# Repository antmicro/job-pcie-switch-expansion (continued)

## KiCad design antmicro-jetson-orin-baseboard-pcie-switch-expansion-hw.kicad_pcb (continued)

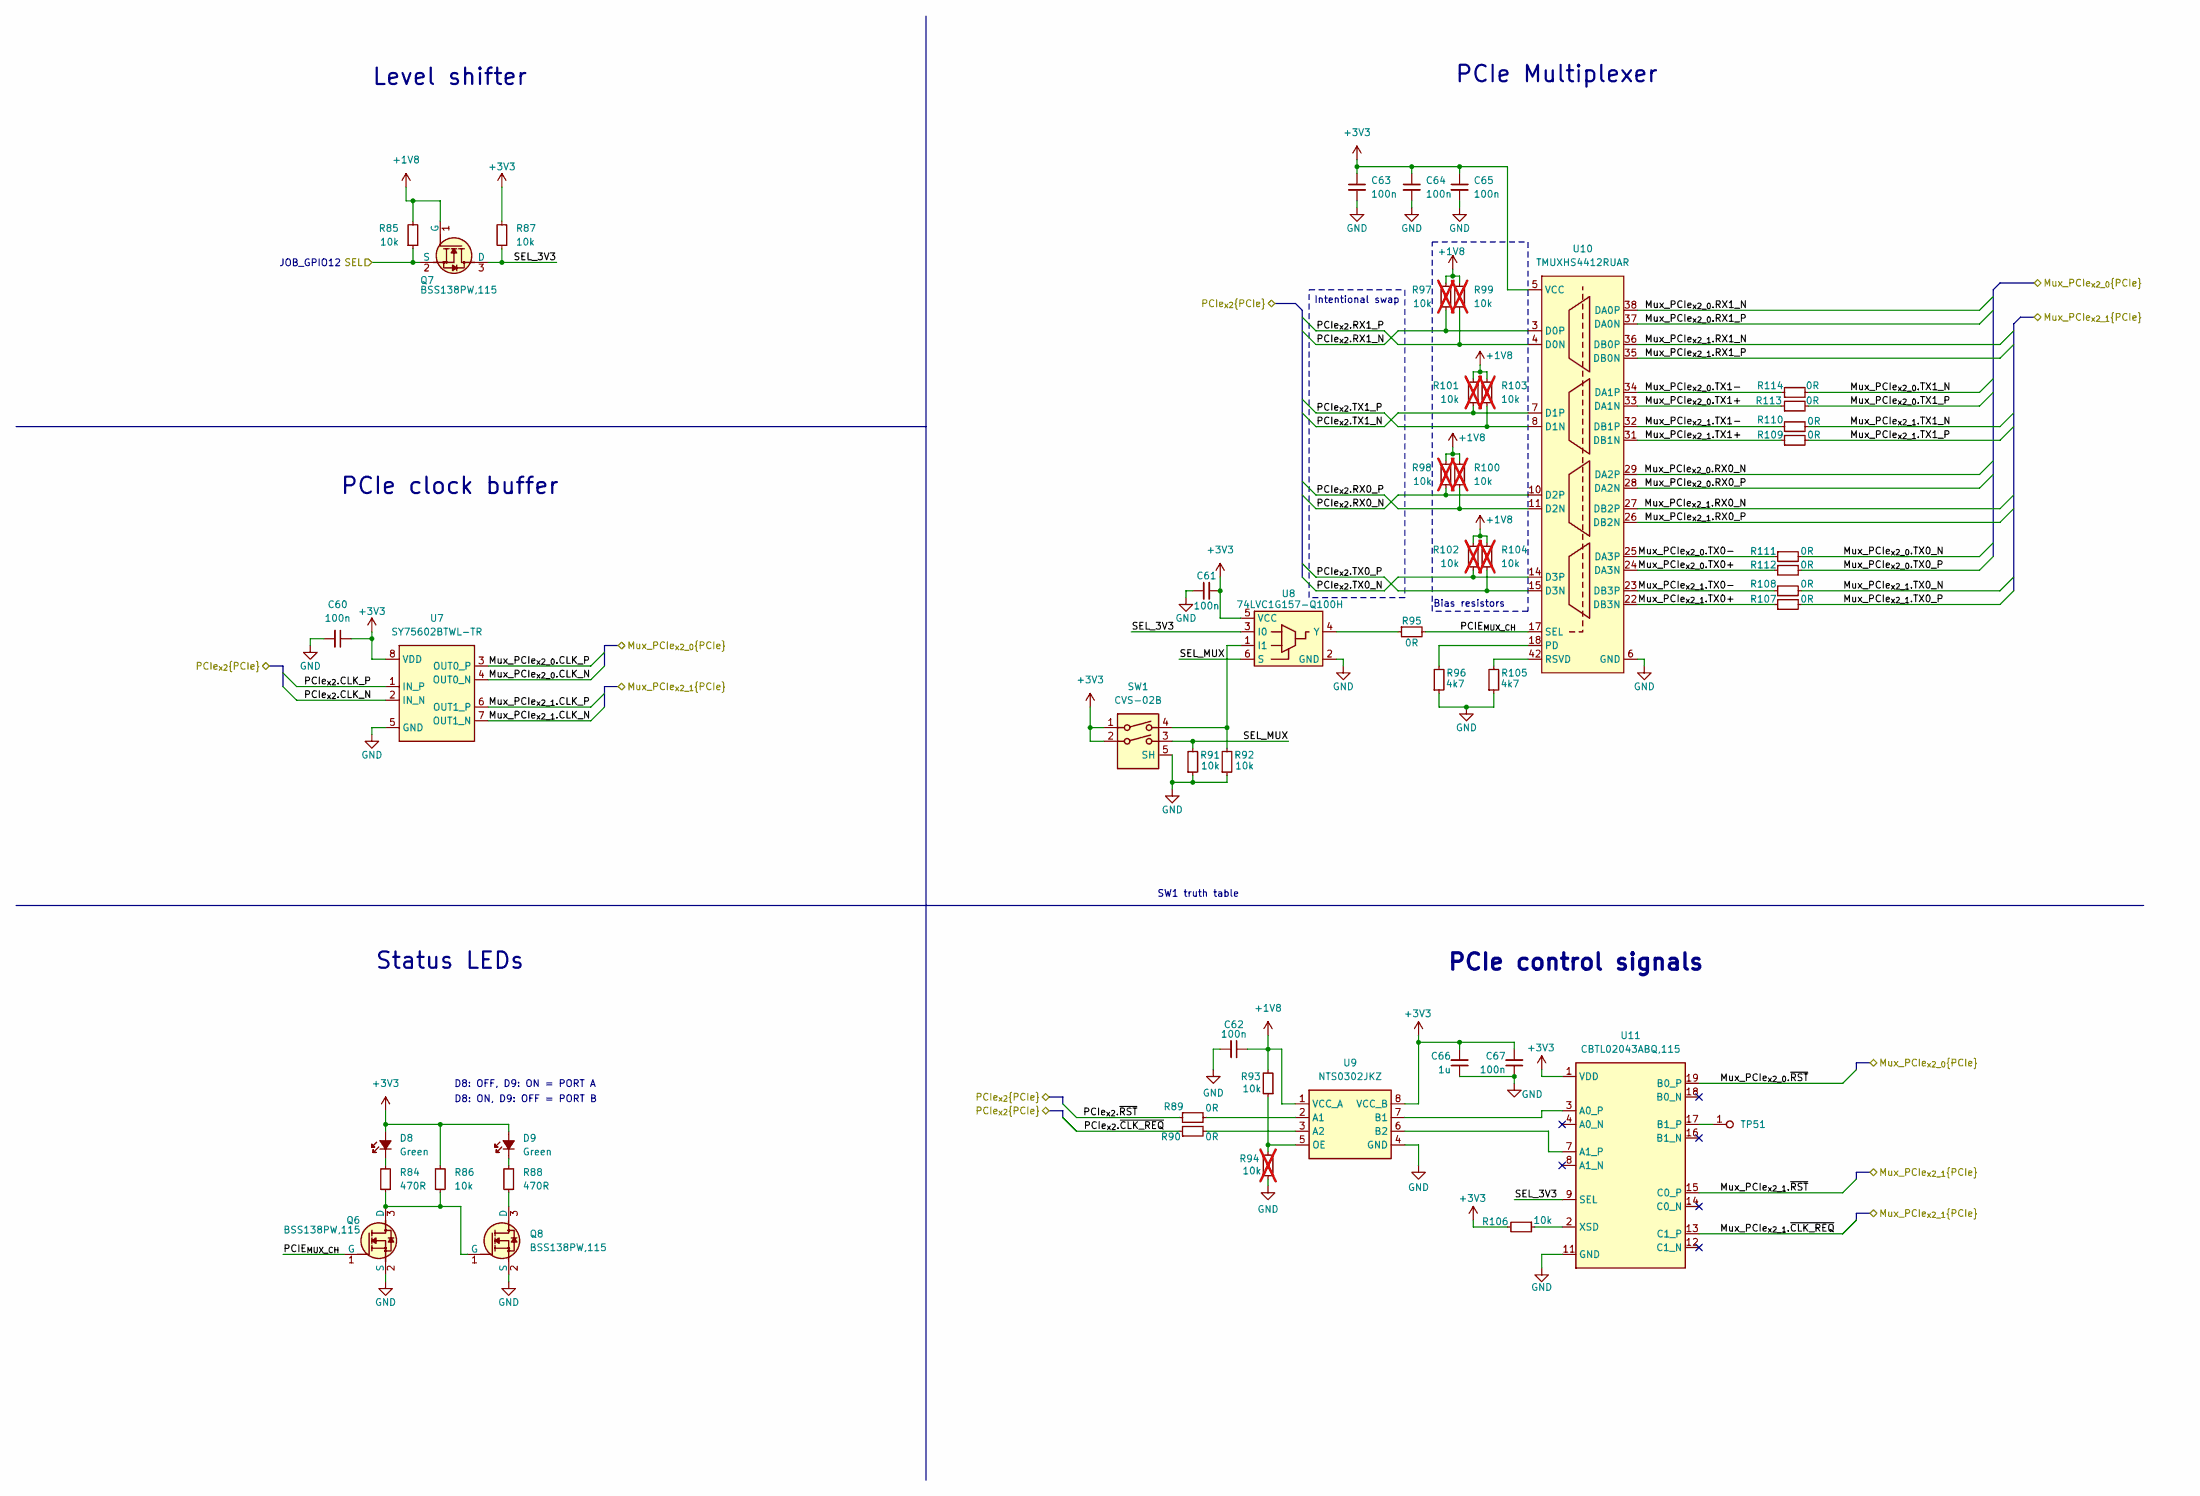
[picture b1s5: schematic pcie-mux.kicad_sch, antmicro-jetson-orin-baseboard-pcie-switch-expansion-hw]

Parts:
C60, C61, C62, C63, C64, C65, C67: C_100n_0402; C_0402_1005Metric; Voltage 50V; MPN GRM155R61H104KE14D
C66: C_1u_0402; C_0402_1005Metric; MPN C1005X6S1A105K050BC
D8, D9: LED_G_0603_LG_L29K-G2J1-24-Z; LED_0603_1608Metric_G; MPN LG L29K-G2J1-24-Z
Q6, Q7, Q8: BSS138PW,115; SC70-3; MPN BSS138PW,115
R84, R88: R_470R_0402; R_0402_1005Metric; Tolerance 1%; MPN CR0402-FX-4700GLF
R85, R86, R87, R91, R92, R93, R106: R_10k_0402; R_0402_1005Metric; Tolerance 1%; MPN CR0402-FX-1002GLF
R89, R90, R95, R107, R108, R109, R110, R111, R112, R113, R114: R_0R_0402; R_0402_1005Metric; MPN ERJ2GE0R00X
R94, R97, R98, R99, R100, R101, R102, R103, R104: R_10k_0402; R_0402_1005Metric; Tolerance 1%; MPN CR0402-FX-1002GLF; not fitted
R96, R105: R_4k7_0402; R_0402_1005Metric; Tolerance 1%; MPN CR0402-FX-4701GLF
SW1: SW_CVS-02B; SW_DIP_SPSTx02_Slide_Copal_CVS-02xB_W5.9mm_P1mm; MPN CVS-02B
TP51: TP_1mm_SMD; TP_SMD_1mm
U7: SY75602BTWL-TR; VDFN-8_1.6x1.4mm_P0.4mm; MPN SY75602BTWL-TR
U8: 74LVC1G157-Q100H_SOT457; SC-74-6_1.5x2.9mm_P0.95mm; MPN 74LVC1G157-Q100H
U9: NTS0302JKZ; X2SON8_1.4x1x0.32mm_P0.35mm; MPN NTS0302JKZ
U10: TMUXHS4412RUAR; WQFN-42-1EP_3.5x9mm_P0.5mm; MPN TMUXHS4412RUAR
U11: CBTL02043ABQ; DHVQFN-20-1EP_2.5x4.5_P0.5mm; MPN CBTL02043ABQ,115

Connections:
+1V8: C62.1, Q7.1 (G), R85.2, R93.2, R97.2, R98.2, R99.2, R100.2, R101.2, R102.2, R103.2, R104.2, U9.1 (VCC_A); also elsewhere on the board
+3V3: C60.1, C61.2, C63.1, C64.1, C65.1, C66.2, C67.2, D8.2 (A), D9.2 (A), R86.2, R87.2, R106.2, SW1.1, SW1.2, U7.8 (VDD), U8.5 (VCC), U9.8 (VCC_B), U10.5 (VCC), U10.13 (VCC), U11.1 (VDD), U11.6 (VDD), U11.10 (VDD); also elsewhere on the board
/Expansion Connector/SEL: Q7.2 (S), R85.1; also elsewhere on the board
/M.2 port B/PCIe_{x2}.CLK_N: U7.7 (OUT1_N); also elsewhere on the board
/M.2 port B/PCIe_{x2}.CLK_P: U7.6 (OUT1_P); also elsewhere on the board
/M.2 port B/PCIe_{x2}.RX0_N: U10.27 (DB2P); also elsewhere on the board
/M.2 port B/PCIe_{x2}.RX0_P: U10.26 (DB2N); also elsewhere on the board
/M.2 port B/PCIe_{x2}.RX1_N: U10.36 (DB0P); also elsewhere on the board
/M.2 port B/PCIe_{x2}.RX1_P: U10.35 (DB0N); also elsewhere on the board
/M.2 port B/PCIe_{x2}.TX0_N: R108.2; also elsewhere on the board
/M.2 port B/PCIe_{x2}.TX0_P: R107.2; also elsewhere on the board
/M.2 port B/PCIe_{x2}.TX1_N: R110.2; also elsewhere on the board
/M.2 port B/PCIe_{x2}.TX1_P: R109.2; also elsewhere on the board
/M.2 port B/PCIe_{x2}.~CLK_REQ: U11.13 (C1_P); also elsewhere on the board
/M.2 port B/PCIe_{x2}.~RST: U11.15 (C0_P); also elsewhere on the board
/OCuLink/PCIe_{x2}.CLK_N: U7.4 (OUT0_N); also elsewhere on the board
/OCuLink/PCIe_{x2}.CLK_P: U7.3 (OUT0_P); also elsewhere on the board
/OCuLink/PCIe_{x2}.RX0_N: U10.29 (DA2P); also elsewhere on the board
/OCuLink/PCIe_{x2}.RX0_P: U10.28 (DA2N); also elsewhere on the board
/OCuLink/PCIe_{x2}.RX1_N: U10.38 (DA0P); also elsewhere on the board
/OCuLink/PCIe_{x2}.RX1_P: U10.37 (DA0N); also elsewhere on the board
/OCuLink/PCIe_{x2}.TX0_N: R111.2; also elsewhere on the board
/OCuLink/PCIe_{x2}.TX0_P: R112.2; also elsewhere on the board
/OCuLink/PCIe_{x2}.TX1_N: R114.2; also elsewhere on the board
/OCuLink/PCIe_{x2}.TX1_P: R113.2; also elsewhere on the board
/OCuLink/PCIe_{x2}.~RST: U11.19 (B0_P); also elsewhere on the board
/PCIe Mux/Mux_PCIe_{x2_0}.TX0+: R112.1, U10.24 (DA3N)
/PCIe Mux/Mux_PCIe_{x2_0}.TX0-: R111.1, U10.25 (DA3P)
/PCIe Mux/Mux_PCIe_{x2_0}.TX1+: R113.1, U10.33 (DA1N)
/PCIe Mux/Mux_PCIe_{x2_0}.TX1-: R114.1, U10.34 (DA1P)
/PCIe Mux/Mux_PCIe_{x2_1}.TX0+: R107.1, U10.22 (DB3N)
/PCIe Mux/Mux_PCIe_{x2_1}.TX0-: R108.1, U10.23 (DB3P)
/PCIe Mux/Mux_PCIe_{x2_1}.TX1+: R109.1, U10.31 (DB1N)
/PCIe Mux/Mux_PCIe_{x2_1}.TX1-: R110.1, U10.32 (DB1P)
/PCIe Mux/PCIE_{MUX_CH}: Q6.1 (G), R95.2, U10.17 (SEL)
/PCIe Mux/PCIe_{x2}.CLK_N: U7.2 (IN_N); also elsewhere on the board
/PCIe Mux/PCIe_{x2}.CLK_P: U7.1 (IN_P); also elsewhere on the board
/PCIe Mux/PCIe_{x2}.RX0_N: R98.1, U10.10 (D2P); also elsewhere on the board
/PCIe Mux/PCIe_{x2}.RX0_P: R100.1, U10.11 (D2N); also elsewhere on the board
/PCIe Mux/PCIe_{x2}.RX1_N: R97.1, U10.3 (D0P); also elsewhere on the board
/PCIe Mux/PCIe_{x2}.RX1_P: R99.1, U10.4 (D0N); also elsewhere on the board
/PCIe Mux/PCIe_{x2}.TX0_N: R102.1, U10.14 (D3P); also elsewhere on the board
/PCIe Mux/PCIe_{x2}.TX0_P: R104.1, U10.15 (D3N); also elsewhere on the board
/PCIe Mux/PCIe_{x2}.TX1_N: R101.1, U10.7 (D1P); also elsewhere on the board
/PCIe Mux/PCIe_{x2}.TX1_P: R103.1, U10.8 (D1N); also elsewhere on the board
/PCIe Mux/PCIe_{x2}.~CLK_REQ: R90.1; also elsewhere on the board
/PCIe Mux/PCIe_{x2}.~RST: R89.1; also elsewhere on the board
/PCIe Mux/SEL_3V3: Q7.3 (D), R87.1, U8.3 (I0), U11.9 (SEL)
/PCIe Mux/SEL_MUX: R91.2, SW1.3, U8.6 (S)
GND: C60.2, C61.1, C62.2, C63.2, C64.2, C65.2, C66.1, C67.1, Q6.2 (S), Q8.2 (S), R91.1, R92.1, R94.1, R96.1, R105.1, SW1.5 (SH_5), U7.5 (GND), U8.2 (GND), U9.4 (GND), U10.6 (GND), U10.9 (GND), U10.16 (GND), U10.21 (GND), U10.30 (GND), U10.39 (GND), U10.43 (GND), U11.5 (GND), U11.11 (GND), U11.20 (GND), U11.21 (GND); also elsewhere on the board
unnamed: D8.1 (C), R84.2
unnamed: D9.1 (C), R88.2
unnamed: Q6.3 (D), Q8.1 (G), R84.1, R86.1
unnamed: Q8.3 (D), R88.1
unnamed: R92.2, SW1.4, U8.1 (I1)
unnamed: R95.1, U8.4 (Y)
unnamed: R89.2, U9.2 (A1)
unnamed: R90.2, U9.3 (A2)
unnamed: R93.1, R94.2, U9.5 (OE)
unnamed: R96.2, U10.18 (PD)
unnamed: R105.2, U10.42 (RSVD)
unnamed: U9.7 (B1), U11.3 (A0_P)
unnamed: U9.6 (B2), U11.7 (A1_P)
unnamed: TP51.1 (1_1), U11.17 (B1_P)
unnamed: R106.1, U11.2 (XSD)

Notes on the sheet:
JOB_GPIO12
Level shifter
PCIe clock buffer
SW1 truth table
PCIe Multiplexer
Bias resistors
Intentional swap
D8: OFF, D9: ON = PORT A
Status LEDs
D8: ON, D9: OFF = PORT B
PCIe control signals

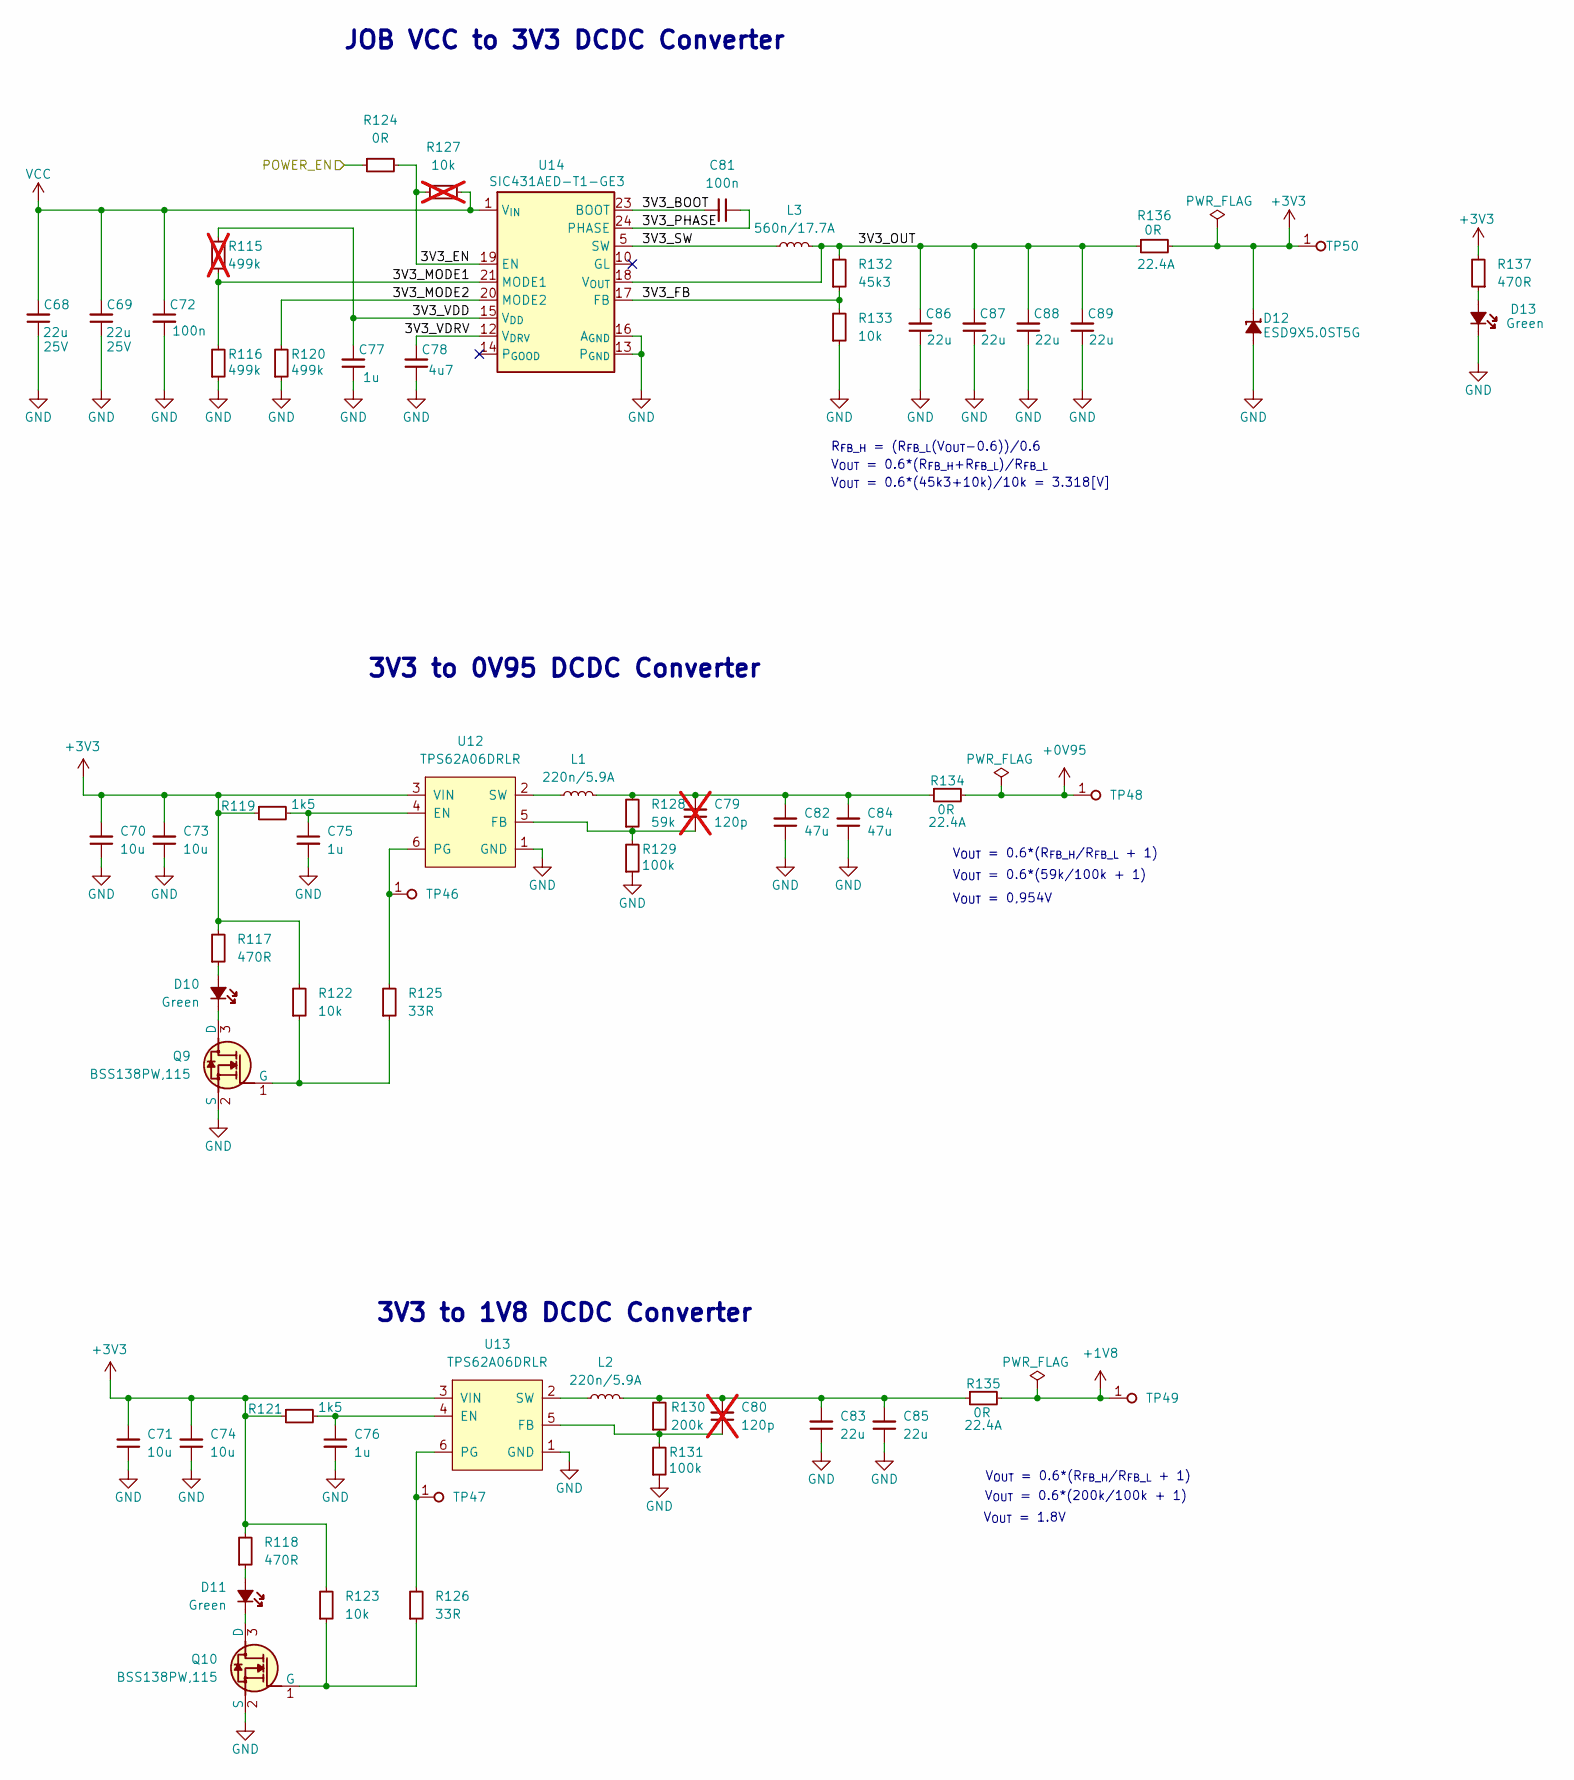
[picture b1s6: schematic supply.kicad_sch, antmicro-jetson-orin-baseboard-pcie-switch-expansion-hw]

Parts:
C68, C69: C_22u_25V_0805; C_0805_2012Metric; Voltage 25V; MPN CL21A226MAYNNNE
C70, C71, C73, C74: C_10u_0402; C_0402_1005Metric; MPN CC0402MRX5R5BB106
C72, C81: C_100n_0402; C_0402_1005Metric; Voltage 50V; MPN GRM155R61H104KE14D
C75, C76, C77: C_1u_0402; C_0402_1005Metric; MPN C1005X6S1A105K050BC
C78: C_4u7_25V_0402; C_0402_1005Metric; Voltage 25V; MPN GRM155C61E475ME15J
C79, C80: C_120p_100V_0402; C_0402_1005Metric; Voltage 100V; MPN C0402C121J5GACTU; not fitted
C82, C84: C_47u_0603; C_0603_1608Metric; MPN GRM188R60J476ME15D
C83, C85: C_22u_0603; C_0603_1608Metric; MPN GRM188R60J226MEA0D
C86, C87, C88, C89: C_22u_16V_0603; C_0603_1608Metric_EIA; Voltage 16V; MPN CL10A226MO7JZNC
D10, D11: LED_G_0603_LG_L29K-G2J1-24-Z; LED_0603_1608Metric_G; MPN LG L29K-G2J1-24-Z
D12: ESD9X5.0ST5G; SOD-923; MPN ESD9X5.0ST5G
D13: LED_G_0603_KP-1608CGCK; LED_0603_1608Metric_G; MPN KP-1608CGCK
L1, L2: L_220n_5.9A_1008; L_1008_2520Metric; MPN SRP2510TMA-R22M
L3: L_560n_17.7A_Bourns-SRP5030CA; L_Bourns-SRP5030CA; MPN SRP5030CA-R56M
Q9, Q10: BSS138PW,115; SC70-3; MPN BSS138PW,115
R115: R_499k_0402; R_0402_1005Metric; Tolerance 1%; MPN CR0402-FX-4993GLF; not fitted
R116, R120: R_499k_0402; R_0402_1005Metric; Tolerance 1%; MPN CR0402-FX-4993GLF
R117, R118, R137: R_470R_0402; R_0402_1005Metric; Tolerance 1%; MPN CR0402-FX-4700GLF
R119, R121: R_1k5_0402; R_0402_1005Metric; Tolerance 1%; MPN CR0402-FX-1501GLF
R122, R123, R133: R_10k_0402; R_0402_1005Metric; Tolerance 1%; MPN CR0402-FX-1002GLF
R124: R_0R_0402; R_0402_1005Metric; MPN ERJ2GE0R00X
R125, R126: R_33R_0402; R_0402_1005Metric; Tolerance 1%; MPN CR0402-FX-33R0GLF
R127: R_10k_0402; R_0402_1005Metric; Tolerance 1%; MPN CR0402-FX-1002GLF; not fitted
R128: R_59k_0402; R_0402_1005Metric; Tolerance 1%; MPN CR0402-FX-5902GLF
R129, R131: R_100k_0.1%_0402; R_0402_1005Metric; Tolerance 1%; MPN CR0402-FX-1003GLF
R130: R_200k_0402; R_0402_1005Metric; Tolerance 1%; MPN CR0402-FX-2003GLF
R132: R_45k3_0402; R_0402_1005Metric; Tolerance 1%; MPN CR0402-FX-4532GLF
R134, R135, R136: R_0R_22.4A_0603; R_0603_1608Metric; Tolerance template_tolerance; MPN PMR03EZPJ000
TP46, TP47, TP48, TP49, TP50: TP_0.75mm_SMD; TP_SMD_0.75mm
U12, U13: TPS62A06DRLR; SOT-563; MPN TPS62A06DRLR
U14: SIC431AED-T1-GE3; MLP44-24L_4x4x0.75mm; MPN SIC431AED-T1-GE3

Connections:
+0V95: R134.2, TP48.1 (1_1); also elsewhere on the board
+1V8: R135.2, TP49.1 (1_1); also elsewhere on the board
+3V3: C70.2, C71.2, C73.2, C74.2, D12.1 (C), R117.2, R118.2, R119.1, R121.1, R122.2, R123.2, R136.2, R137.2, TP50.1 (1_1), U12.3 (VIN), U13.3 (VIN); also elsewhere on the board
/Expansion Connector/POWER_EN: R124.1; also elsewhere on the board
/Supply/3V3_BOOT: C81.2, U14.23 (BOOT)
/Supply/3V3_EN: R124.2, R127.2, U14.19 (EN)
/Supply/3V3_FB: R132.1, R133.2, U14.17 (FB)
/Supply/3V3_MODE1: R115.1, R116.2, U14.21 (MODE1)
/Supply/3V3_MODE2: R120.2, U14.20 (MODE2)
/Supply/3V3_OUT: C86.2, C87.2, C88.2, C89.2, L3.2, R132.2, R136.1, U14.18 (V_{OUT})
/Supply/3V3_PHASE: C81.1, U14.24 (PHASE)
/Supply/3V3_SW: L3.1, U14.5 (SW), U14.6 (SW), U14.7 (SW), U14.8 (SW), U14.9 (SW)
/Supply/3V3_VDD: C77.2, R115.2, U14.15 (V_{DD})
/Supply/3V3_VDRV: C78.2, U14.12 (V_{DRV})
GND: C68.1, C69.1, C70.1, C71.1, C72.2, C73.1, C74.1, C75.2, C76.2, C77.1, C78.1, C82.1, C83.1, C84.1, C85.1, C86.1, C87.1, C88.1, C89.1, D12.2 (A), D13.1 (C), Q9.2 (S), Q10.2 (S), R116.1, R120.1, R129.1, R131.1, R133.1, U12.1 (GND), U13.1 (GND), U14.3 (P_{GND}), U14.4 (P_{GND}), U14.13 (P_{GND}), U14.16 (A_{GND}), U14.25 (A_{GND}), U14.27 (P_{GND}); also elsewhere on the board
unnamed: C79.2, C82.2, C84.2, L1.2, R128.2, R134.1
unnamed: C80.2, C83.2, C85.2, L2.2, R130.2, R135.1
unnamed: D10.2 (A), R117.1
unnamed: D10.1 (C), Q9.3 (D)
unnamed: D11.2 (A), R118.1
unnamed: D11.1 (C), Q10.3 (D)
unnamed: D13.2 (A), R137.1
unnamed: Q9.1 (G), R122.1, R125.1
unnamed: Q10.1 (G), R123.1, R126.1
unnamed: C75.1, R119.2, U12.4 (EN)
unnamed: C79.1, R128.1, R129.2, U12.5 (FB)
unnamed: R125.2, TP46.1 (1_1), U12.6 (PG)
unnamed: L1.1, U12.2 (SW)
unnamed: C76.1, R121.2, U13.4 (EN)
unnamed: C80.1, R130.1, R131.2, U13.5 (FB)
unnamed: R126.2, TP47.1 (1_1), U13.6 (PG)
unnamed: L2.1, U13.2 (SW)
VCC: C68.2, C69.2, C72.1, R127.1, U14.1 (V_{IN}), U14.2 (V_{IN}), U14.22 (V_{IN}), U14.26 (V_{IN}); also elsewhere on the board

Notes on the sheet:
3V3 to 1V8 DCDC Converter
V_{OUT} = 0.6*(R_{FB_H}+R_{FB_L})/R_{FB_L}
R_{FB_H} = (R_{FB_L}(V_{OUT}-0.6))/0.6
V_{OUT} = 0.6*(45k3+10k)/10k = 3.318[V]
V_{OUT} = 0.6*(R_{FB_H}/R_{FB_L} + 1)
V_{OUT} = 0.6*(59k/100k + 1)
3V3 to 0V95 DCDC Converter
JOB VCC to 3V3 DCDC Converter
V_{OUT} = 0,954V
V_{OUT} = 1.8V
V_{OUT} = 0.6*(200k/100k + 1)

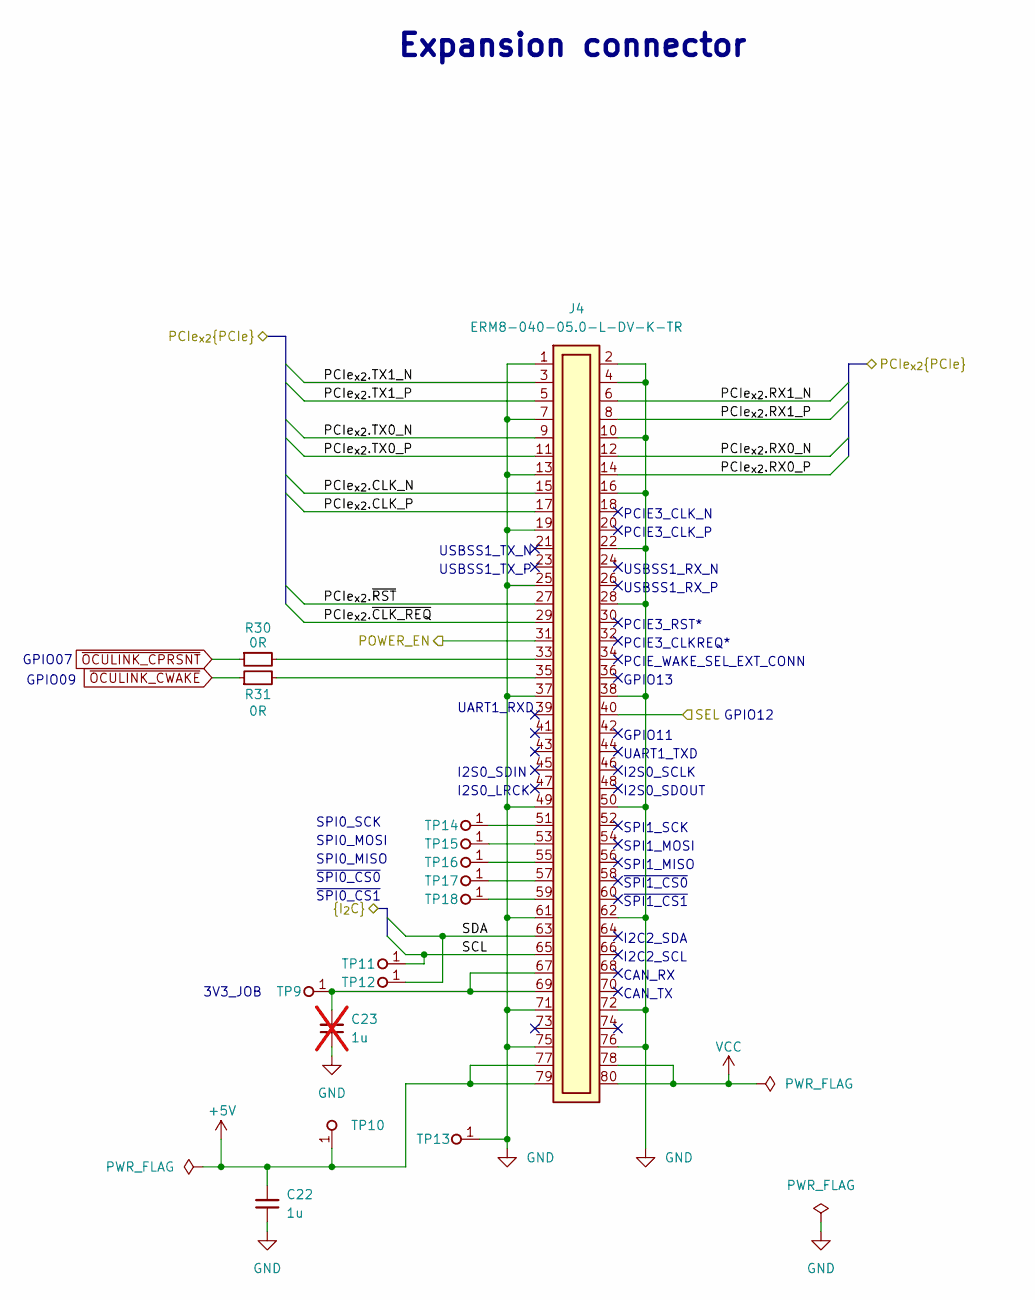
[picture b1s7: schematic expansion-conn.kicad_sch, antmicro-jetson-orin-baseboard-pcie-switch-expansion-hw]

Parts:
C22: C_1u_0402; C_0402_1005Metric; MPN C1005X6S1A105K050BC
C23: C_1u_0402; C_0402_1005Metric; MPN C1005X6S1A105K050BC; not fitted
J4: Plug_Samtec_ERM8_2x40_ERM8-040-05.0-L-DV-K-TR; Conn_Plug_Samtec_ERM8_2x40_ERM8-040-05.0-L-DV-K-TR; MPN ERM8-040-05.0-L-DV-K-TR
R30, R31: R_0R_0402; R_0402_1005Metric; MPN ERJ2GE0R00X
TP9, TP10, TP11, TP12, TP13, TP14, TP15, TP16, TP17, TP18: TP_0.75mm_SMD; TP_SMD_0.75mm

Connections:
+5V: C22.2, J4.77, J4.79, TP10.1 (1_1); also elsewhere on the board
/Expansion Connector/PCIe_{x2}.CLK_N: J4.15; also elsewhere on the board
/Expansion Connector/PCIe_{x2}.CLK_P: J4.17; also elsewhere on the board
/Expansion Connector/PCIe_{x2}.RX0_N: J4.12; also elsewhere on the board
/Expansion Connector/PCIe_{x2}.RX0_P: J4.14; also elsewhere on the board
/Expansion Connector/PCIe_{x2}.RX1_N: J4.6; also elsewhere on the board
/Expansion Connector/PCIe_{x2}.RX1_P: J4.8; also elsewhere on the board
/Expansion Connector/PCIe_{x2}.TX0_N: J4.9; also elsewhere on the board
/Expansion Connector/PCIe_{x2}.TX0_P: J4.11; also elsewhere on the board
/Expansion Connector/PCIe_{x2}.TX1_N: J4.3; also elsewhere on the board
/Expansion Connector/PCIe_{x2}.TX1_P: J4.5; also elsewhere on the board
/Expansion Connector/PCIe_{x2}.~CLK_REQ: J4.29; also elsewhere on the board
/Expansion Connector/PCIe_{x2}.~RST: J4.27; also elsewhere on the board
/Expansion Connector/POWER_EN: J4.31; also elsewhere on the board
/Expansion Connector/SCL: J4.65, TP11.1 (1_1); also elsewhere on the board
/Expansion Connector/SDA: J4.63, TP12.1 (1_1); also elsewhere on the board
/Expansion Connector/SEL: J4.40; also elsewhere on the board
GND: C22.1, C23.1, J4.1, J4.2, J4.4, J4.7, J4.10, J4.13, J4.16, J4.19, J4.22, J4.25, J4.28, J4.37, J4.38, J4.49, J4.50, J4.61, J4.62, J4.71, J4.72, J4.75, J4.76, TP13.1 (1_1); also elsewhere on the board
unnamed: C23.2, J4.67, J4.69, TP9.1 (1_1)
unnamed: J4.33, R30.2
unnamed: J4.35, R31.2
unnamed: J4.51, TP14.1 (1_1)
unnamed: J4.53, TP15.1 (1_1)
unnamed: J4.55, TP16.1 (1_1)
unnamed: J4.57, TP17.1 (1_1)
unnamed: J4.59, TP18.1 (1_1)
VCC: J4.78, J4.80; also elsewhere on the board
~OCULINK_CPRSNT: R30.1; also elsewhere on the board
~OCULINK_CWAKE: R31.1; also elsewhere on the board

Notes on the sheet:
USBSS1_RX_P
~{SPI1_CS1}
SPI0_MOSI
UART1_RXD
I2S0_SDOUT
PCIE3_CLK_N
~{SPI0_CS0}
I2S0_SDIN
USBSS1_RX_N
GPIO07
CAN_TX
PCIE3_CLK_P
SPI0_MISO
~{SPI0_CS1}
I2S0_LRCK
PCIE3_CLKREQ*
USBSS1_TX_P
I2C2_SCL
SPI1_MISO
SPI0_SCK
UART1_TXD
GPIO11
SPI1_MOSI
PCIE3_RST*
I2C2_SDA
~{SPI1_CS0}
GPIO13
CAN_RX
GPIO12
PCIE_WAKE_SEL_EXT_CONN
Expansion connector
USBSS1_TX_N
GPIO09
3V3_JOB
I2S0_SCLK
SPI1_SCK

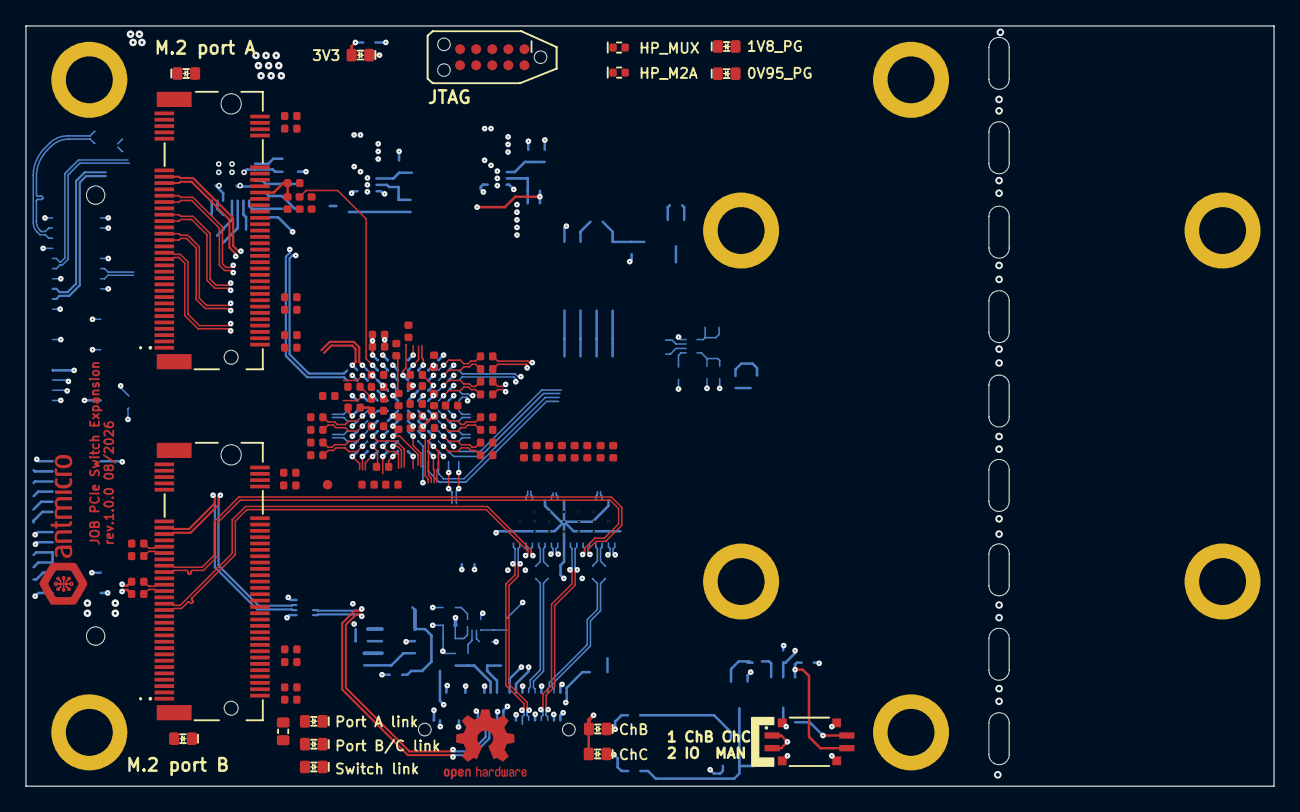
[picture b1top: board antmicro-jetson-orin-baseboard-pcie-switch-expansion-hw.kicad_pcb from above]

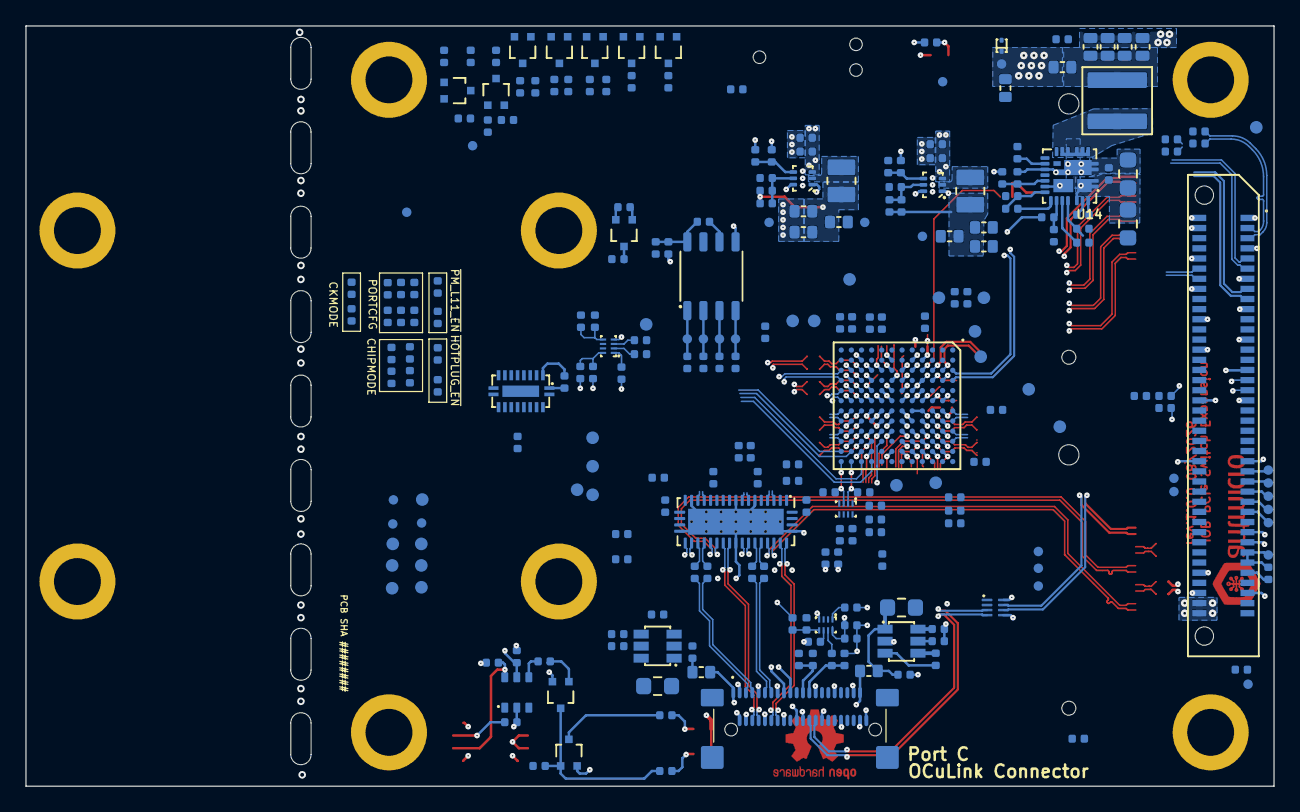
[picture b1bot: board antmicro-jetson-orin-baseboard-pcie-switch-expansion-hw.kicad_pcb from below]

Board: 6 copper layers, 98.5 x 60.0 mm, 341 parts (251 on the bottom side), 253 nets.
